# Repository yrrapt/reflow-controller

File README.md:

# reflow-controller
Quick reflow oven controller design

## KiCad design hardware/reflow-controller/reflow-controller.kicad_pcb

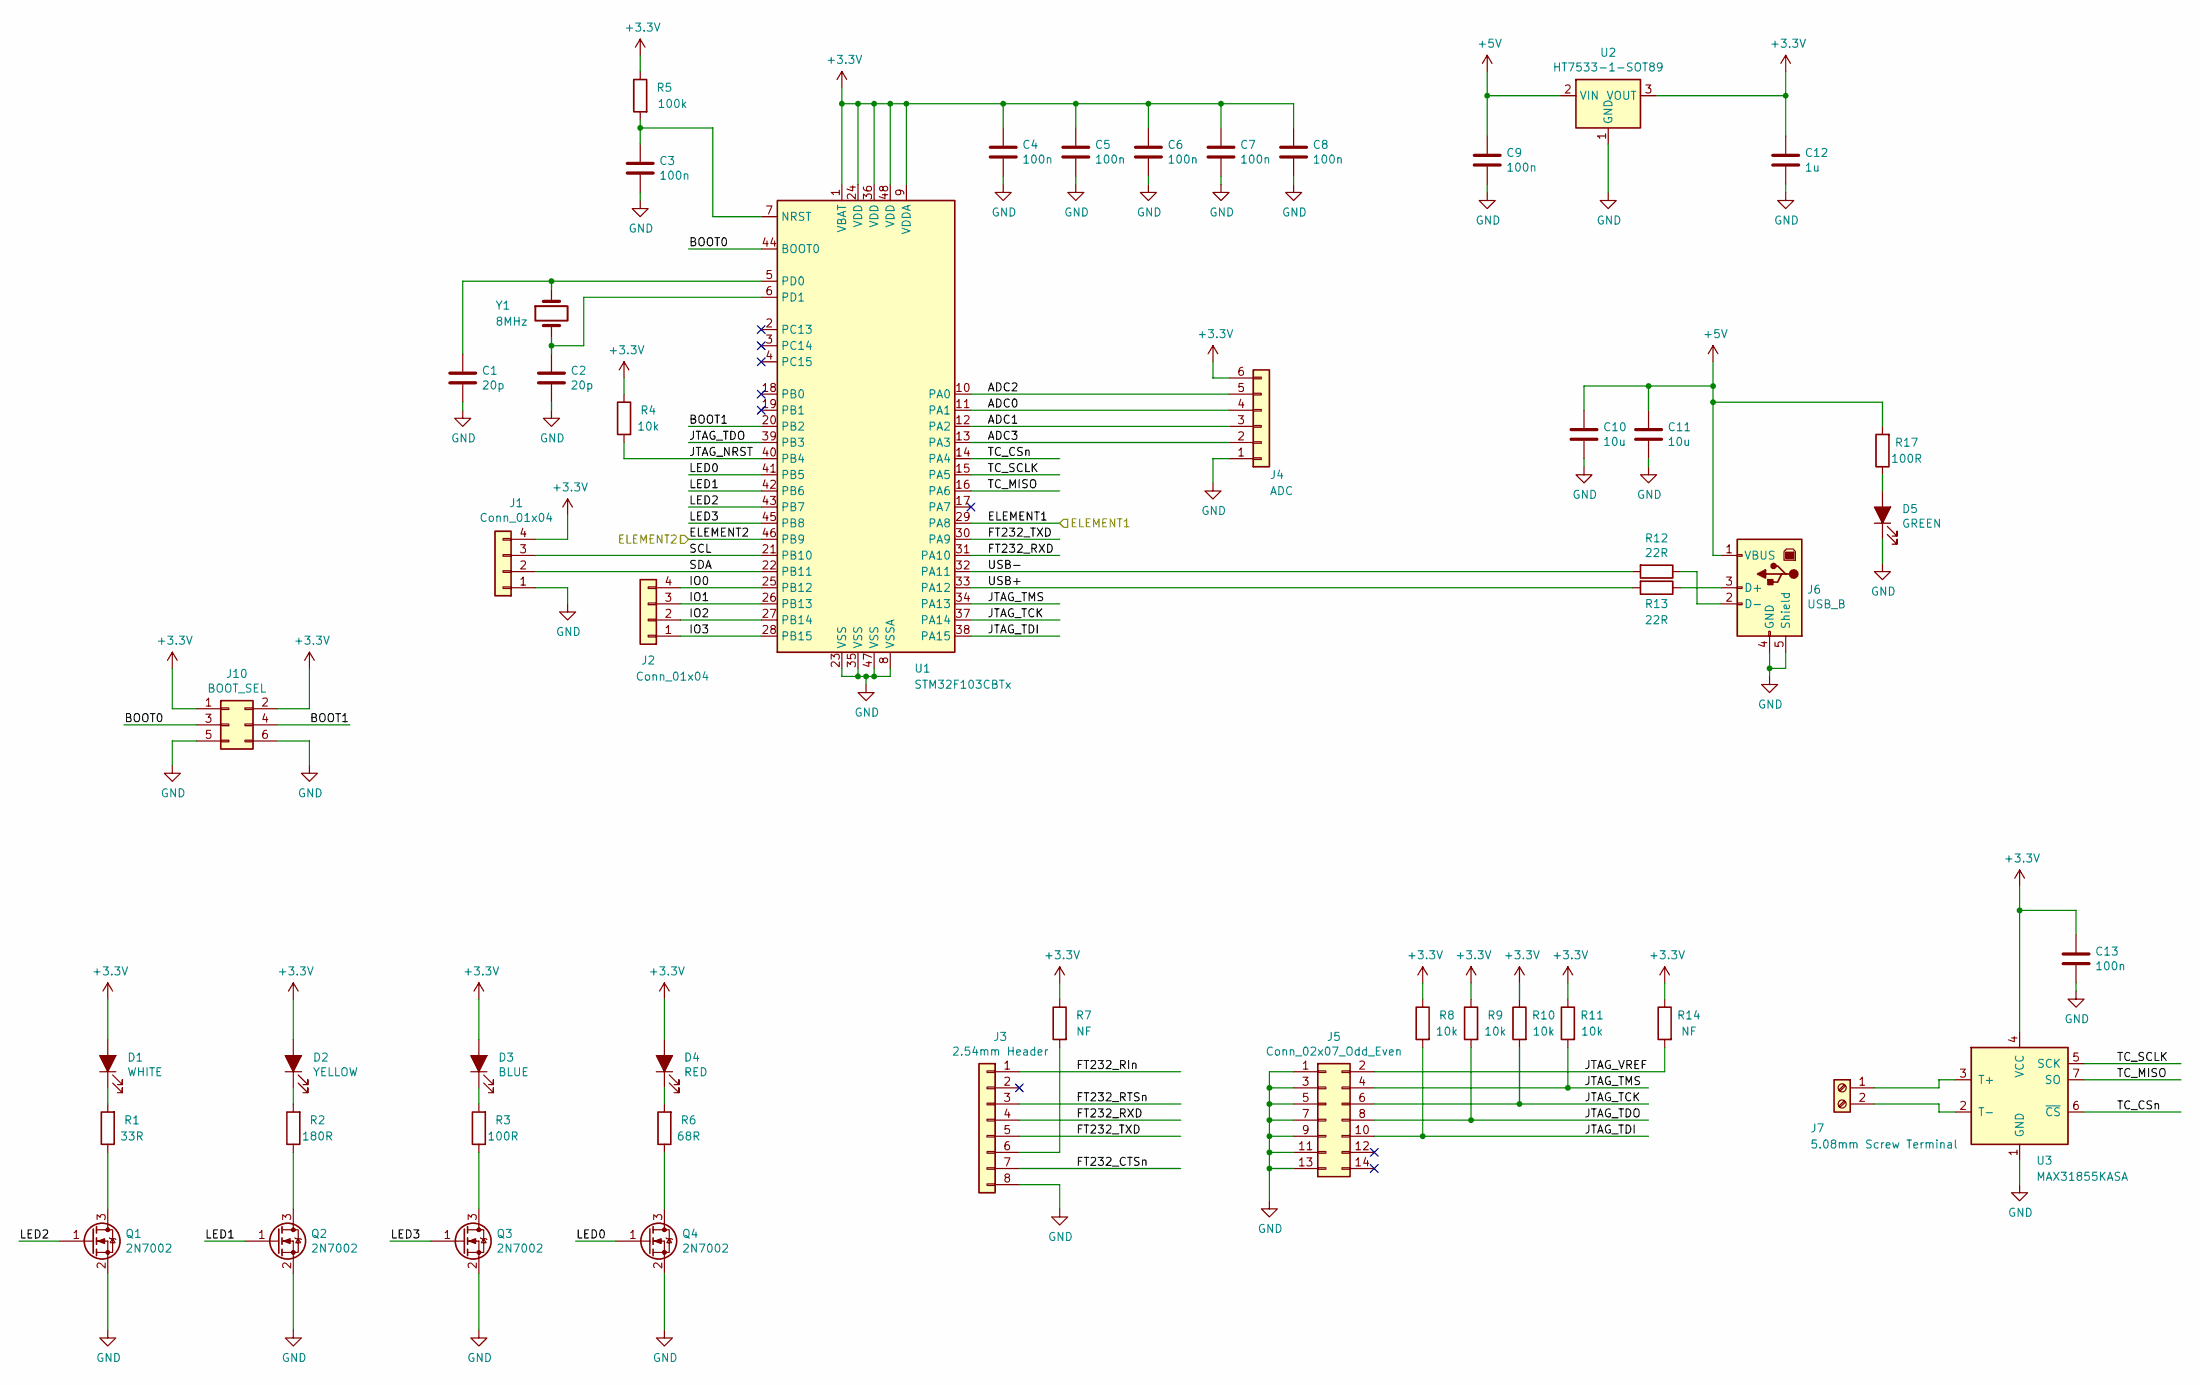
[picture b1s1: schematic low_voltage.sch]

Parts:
C1, C2: 20p; C_0603_1608Metric; LCSC Part # C1648
C3, C4, C5, C6, C7, C8, C9, C13: 100n; C_0603_1608Metric; LCSC Part # C14663
C10, C11: 10u; C_1206_3216Metric; LCSC Part # C13585
C12: 1u; C_1206_3216Metric; LCSC Part # C1848
D1: WHITE; LED_0603_1608Metric; LCSC Part # C2290
D2: YELLOW; LED_0603_1608Metric; LCSC Part # C72038
D3: BLUE; LED_0603_1608Metric; LCSC Part # C72041
D4: RED; LED_0603_1608Metric; LCSC Part # C2286
D5: GREEN; LED_0603_1608Metric; LCSC Part # C72043
J1, J2: Conn_01x04; PinHeader_1x04_P2.54mm_Vertical
J3: 2.54mm Header; PinHeader_1x08_P2.54mm_Vertical
J4: ADC; PinHeader_1x06_P2.54mm_Vertical
J5: Conn_02x07_Odd_Even; PinHeader_2x07_P2.00mm_Vertical_SMD
J6: USB_B; USB_B_OST_USB-B1HSxx_Horizontal
J7: 5.08mm Screw Terminal; TerminalBlock_bornier-2_P5.08mm
J10: BOOT_SEL; PinSocket_2x03_P2.54mm_Vertical
Q1, Q2, Q3, Q4: 2N7002; SOT-23; LCSC Part # C8545
R1: 33R; R_0603_1608Metric; LCSC Part # C23140
R2: 180R; R_0603_1608Metric; LCSC Part # C22828
R3, R17: 100R; R_0603_1608Metric; LCSC Part # C22775
R4, R8, R9, R10, R11: 10k; R_0603_1608Metric; LCSC Part # C25804
R5: 100k; R_0603_1608Metric; LCSC Part # C25803
R6: 68R; R_0603_1608Metric; LCSC Part # C27592
R7, R14: NF; R_0603_1608Metric
R12, R13: 22R; R_0603_1608Metric; LCSC Part # C23345
U1: STM32F103CBTx; LQFP-48_7x7mm_P0.5mm; LCSC Part # C8304
U2: HT7533-1-SOT89; SOT-89-3; LCSC Part # C14289
U3: MAX31855KASA; SOIC-8_3.9x4.9mm_P1.27mm; LCSC Part # C52028
Y1: 8MHz; Crystal_SMD_5032-2Pin_5.0x3.2mm; LCSC Part # C115962

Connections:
+3V3: C4.1, C5.1, C6.1, C7.1, C8.1, C12.1, C13.1, D1.2 (A), D2.2 (A), D3.2 (A), D4.2 (A), J1.4, J4.6, J10.1, J10.2, R4.1, R5.1, R7.1, R8.1, R9.1, R10.1, R11.1, R14.1, U1.1 (VBAT), U1.9 (VDDA), U1.24 (VDD), U1.36 (VDD), U1.48 (VDD), U2.3 (VOUT), U3.4 (VCC); also elsewhere on the board
+5V: C9.1, C10.1, C11.1, J6.1 (VBUS), R17.2, U2.2 (VIN)
/High Voltage/ELEMENT1: U1.29 (PA8); also elsewhere on the board
/High Voltage/ELEMENT2: U1.46 (PB9); also elsewhere on the board
/Low Voltage/ADC0: J4.4, U1.11 (PA1)
/Low Voltage/ADC1: J4.3, U1.12 (PA2)
/Low Voltage/ADC2: J4.5, U1.10 (PA0)
/Low Voltage/ADC3: J4.2, U1.13 (PA3)
/Low Voltage/BOOT0: J10.3, U1.44 (BOOT0)
/Low Voltage/BOOT1: J10.4, U1.20 (PB2)
/Low Voltage/FT232_CTSn: J3.7
/Low Voltage/FT232_RIn: J3.1
/Low Voltage/FT232_RTSn: J3.3
/Low Voltage/FT232_RXD: J3.4, U1.31 (PA10)
/Low Voltage/FT232_TXD: J3.5, U1.30 (PA9)
/Low Voltage/IO0: J2.4, U1.25 (PB12)
/Low Voltage/IO1: J2.3, U1.26 (PB13)
/Low Voltage/IO2: J2.2, U1.27 (PB14)
/Low Voltage/IO3: J2.1, U1.28 (PB15)
/Low Voltage/JTAG_NRST: R4.2, U1.40 (PB4)
/Low Voltage/JTAG_TCK: J5.6, R10.2, U1.37 (PA14)
/Low Voltage/JTAG_TDI: J5.10, R8.2, U1.38 (PA15)
/Low Voltage/JTAG_TDO: J5.8, R9.2, U1.39 (PB3)
/Low Voltage/JTAG_TMS: J5.4, R11.2, U1.34 (PA13)
/Low Voltage/JTAG_VREF: J5.2, R14.2
/Low Voltage/LED0: Q4.1 (G), U1.41 (PB5)
/Low Voltage/LED1: Q2.1 (G), U1.42 (PB6)
/Low Voltage/LED2: Q1.1 (G), U1.43 (PB7)
/Low Voltage/LED3: Q3.1 (G), U1.45 (PB8)
/Low Voltage/SCL: J1.3, U1.21 (PB10)
/Low Voltage/SDA: J1.2, U1.22 (PB11)
/Low Voltage/TC_CSn: U1.14 (PA4), U3.6 (~CS~)
/Low Voltage/TC_MISO: U1.16 (PA6), U3.7 (SO)
/Low Voltage/TC_SCLK: U1.15 (PA5), U3.5 (SCK)
/Low Voltage/USB+: R13.2, U1.33 (PA12)
/Low Voltage/USB-: R12.2, U1.32 (PA11)
GND: C1.2, C2.2, C3.2, C4.2, C5.2, C6.2, C7.2, C8.2, C9.2, C10.2, C11.2, C12.2, C13.2, D5.1 (K), J1.1, J3.8, J4.1, J5.1, J5.3, J5.5, J5.7, J5.9, J5.11, J5.13, J6.4 (GND), J6.5 (Shield), J10.5, J10.6, Q1.2 (S), Q2.2 (S), Q3.2 (S), Q4.2 (S), U1.8 (VSSA), U1.23 (VSS), U1.35 (VSS), U1.47 (VSS), U2.1 (GND), U3.1 (GND); also elsewhere on the board
unnamed: C1.1, U1.5 (PD0), Y1.1
unnamed: C2.1, U1.6 (PD1), Y1.2
unnamed: C3.1, R5.2, U1.7 (NRST)
unnamed: D1.1 (K), R1.2
unnamed: D2.1 (K), R2.2
unnamed: D3.1 (K), R3.2
unnamed: D4.1 (K), R6.2
unnamed: D5.2 (A), R17.1
unnamed: J3.6, R7.2
unnamed: J6.2 (D-), R12.1
unnamed: J6.3 (D+), R13.1
unnamed: J7.1, U3.3 (T+)
unnamed: J7.2, U3.2 (T-)
unnamed: Q1.3 (D), R1.1
unnamed: Q2.3 (D), R2.1
unnamed: Q3.3 (D), R3.1
unnamed: Q4.3 (D), R6.1

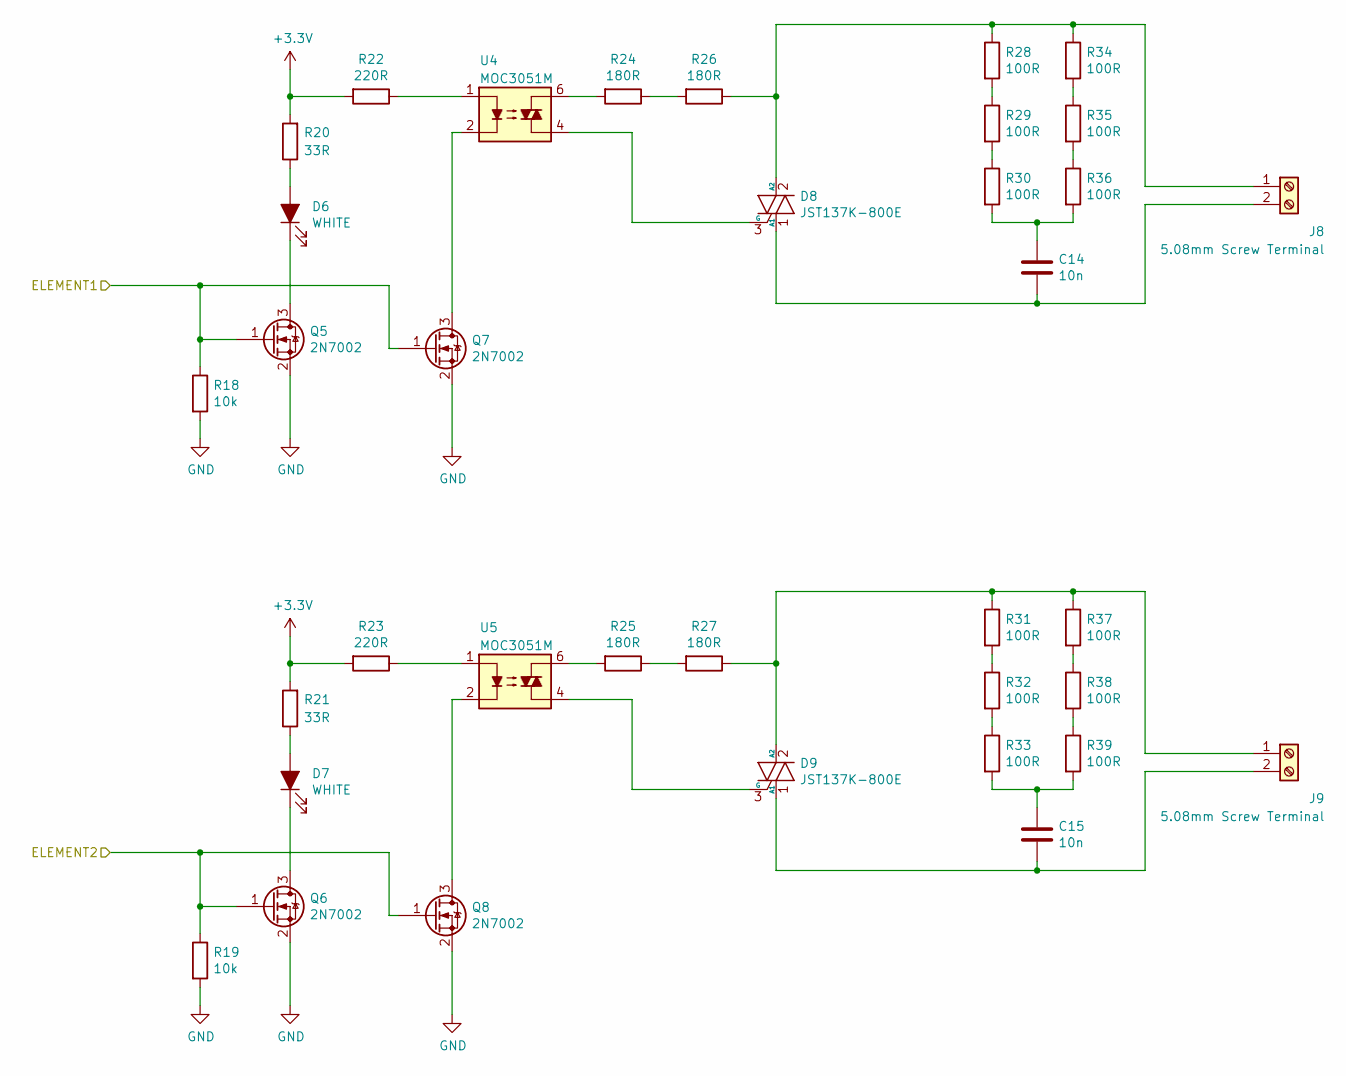
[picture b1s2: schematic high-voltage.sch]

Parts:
C14, C15: 10n; C_0603_1608Metric; LCSC Part # C57112
D6, D7: WHITE; LED_0603_1608Metric; LCSC Part # C2290
D8, D9: JST137K-800E; TO-252-2; LCSC Part # C179477
J8, J9: 5.08mm Screw Terminal; TerminalBlock_bornier-2_P5.08mm
Q5, Q6, Q7, Q8: 2N7002; SOT-23; LCSC Part # C8545
R18, R19: 10k; R_0603_1608Metric; LCSC Part # C25804
R20, R21: 33R; R_0603_1608Metric; LCSC Part # C23140
R22, R23: 220R; R_0603_1608Metric; LCSC Part # C22962
R24, R25, R26, R27: 180R; R_1206_3216Metric; LCSC Part # C17924
R28, R29, R30, R31, R32, R33, R34, R35, R36, R37, R38, R39: 100R; R_1206_3216Metric; LCSC Part # C17901
U4, U5: MOC3051M; DIP-6_W8.89mm_SMDSocket_LongPads; LCSC Part # C184543

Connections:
+3V3: R20.2, R21.2, R22.2, R23.2; also elsewhere on the board
/High Voltage/ELEMENT1: Q5.1 (G), Q7.1 (G), R18.1; also elsewhere on the board
/High Voltage/ELEMENT2: Q6.1 (G), Q8.1 (G), R19.1; also elsewhere on the board
GND: Q5.2 (S), Q6.2 (S), Q7.2 (S), Q8.2 (S), R18.2, R19.2; also elsewhere on the board
unnamed: C14.1, R30.2, R36.2
unnamed: C14.2, D8.1 (A1), J8.2
unnamed: C15.1, R33.2, R39.2
unnamed: C15.2, D9.1 (A1), J9.2
unnamed: D6.1 (K), Q5.3 (D)
unnamed: D6.2 (A), R20.1
unnamed: D7.1 (K), Q6.3 (D)
unnamed: D7.2 (A), R21.1
unnamed: D8.2 (A2), J8.1, R26.1, R28.1, R34.1
unnamed: D8.3 (G), U4.4
unnamed: D9.2 (A2), J9.1, R27.1, R31.1, R37.1
unnamed: D9.3 (G), U5.4
unnamed: Q7.3 (D), U4.2
unnamed: Q8.3 (D), U5.2
unnamed: R22.1, U4.1
unnamed: R23.1, U5.1
unnamed: R24.1, R26.2
unnamed: R24.2, U4.6
unnamed: R25.1, R27.2
unnamed: R25.2, U5.6
unnamed: R28.2, R29.1
unnamed: R29.2, R30.1
unnamed: R31.2, R32.1
unnamed: R32.2, R33.1
unnamed: R34.2, R35.1
unnamed: R35.2, R36.1
unnamed: R37.2, R38.1
unnamed: R38.2, R39.1

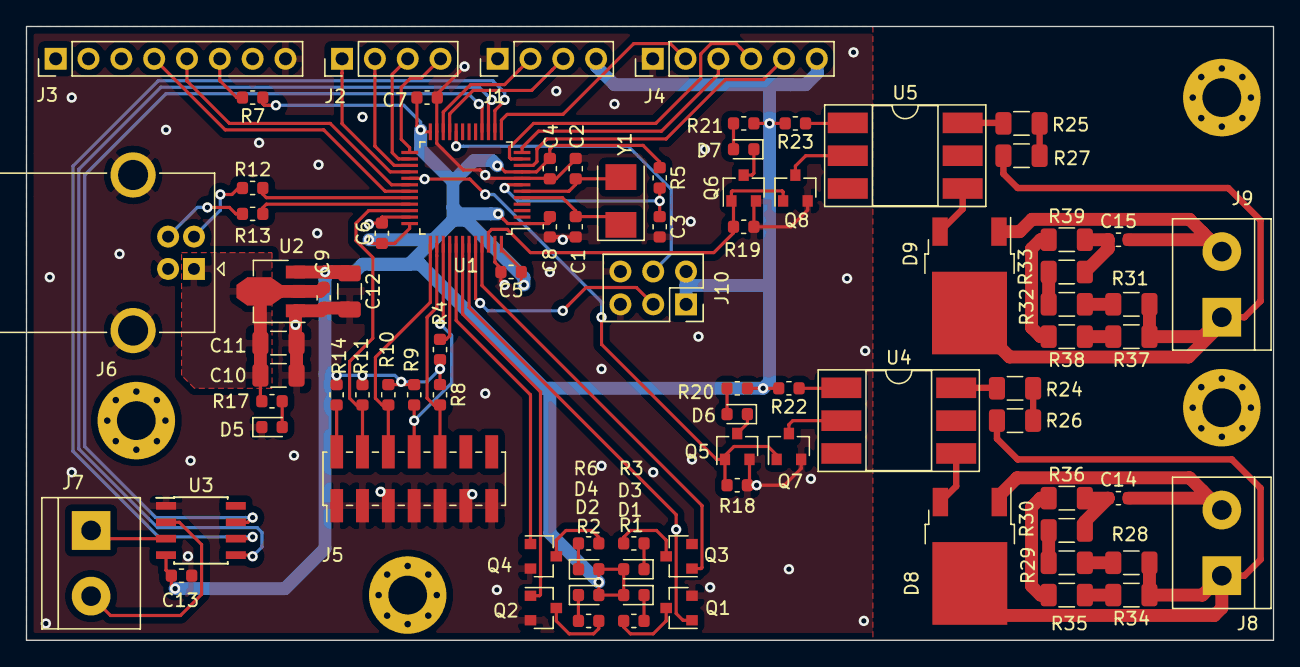
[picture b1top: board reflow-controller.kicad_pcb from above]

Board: 2 copper layers, 96.5 x 47.5 mm, 85 parts (0 on the bottom side), 79 nets.

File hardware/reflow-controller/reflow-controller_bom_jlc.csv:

Comment,Designator,Footprint,LCSC Part #
20p,"C2,C1",C_0603_1608Metric,C1648
100n,"C9,C4,C5,C6,C7,C8,C3,C13",C_0603_1608Metric,C14663
10u,"C11,C10",C_1206_3216Metric,C13585
1u,C12,C_1206_3216Metric,C1848
10n,"C14,C15",C_0603_1608Metric,C57112
WHITE,"D1,D6,D7",LED_0603_1608Metric,C2290
YELLOW,D2,LED_0603_1608Metric,C72038
BLUE,D3,LED_0603_1608Metric,C72041
RED,D4,LED_0603_1608Metric,C2286
GREEN,D5,LED_0603_1608Metric,C72043
JST137K-800E,"D8,D9",TO-252-2,C179477
2N7002,"Q1,Q2,Q3,Q4,Q7,Q5,Q8,Q6",SOT-23,C8545
33R,"R1,R20,R21",R_0603_1608Metric,C23140
180R,R2,R_0603_1608Metric,C22828
100k,R5,R_0603_1608Metric,C25803
68R,R6,R_0603_1608Metric,C27592
10k,"R8,R9,R10,R11,R4,R18,R19",R_0603_1608Metric,C25804
22R,"R12,R13",R_0603_1608Metric,C23345
100R,"R17,R3",R_0603_1608Metric,C22775
220R,"R22,R23",R_0603_1608Metric,C22962
180R,"R24,R26,R25,R27",R_1206_3216Metric,C17924
100R,"R30,R29,R28,R36,R35,R34,R33,R32,R31,R39,R38,R37",R_1206_3216Metric,C17901
STM32F103CBTx,U1,LQFP-48_7x7mm_P0.5mm,C8304
HT7533-1-SOT89,U2,SOT-89-3,C14289
MAX31855KASA+T,U3,SOIC-8_3.9x4.9mm_P1.27mm,C52028
MOC3051SR2VM,"U4,U5",DIP-6_W8.89mm_SMDSocket_LongPads,C184543
8MHz,Y1,Crystal_SMD_5032-2Pin_5.0x3.2mm,C115962

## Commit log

2020-05-01 PCB complete and ordered
2020-05-31 Fixed error with shorting 5V and GND
2020-06-09 Working implementation of turning the oven on and off by software
2020-06-13 Restructed project by putting board into local folder and building directly rather than sym-linking to Zephyr install. Moved thermocouple to driver module
2020-06-13 Updated README to reflect the actual project
